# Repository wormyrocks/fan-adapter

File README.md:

# USB-PD fan driver

This is a completely untested, mostly routed PCB that uses a cheap MCU to trigger a 12V USB-PD sink, to drive a computer box fan. Entire BOM cost should only be $2-$3, no uncommon components. Might have to hand-solder the fan header. You could also use an angled fan header if you wanted.

I started designing this because I was annoyed about not having a desktop fume extractor that I could easily run off a laptop charger. I got busy / lazy and don't actually want to finish it, but if someone wants to adopt it that would be awesome! I have a handful of the CH32X035 preordered on JLCPCB, so the riskiest $10 of the project budget is already a sunk cost.

I designed this with 12V PWM fans in mind, but it occurs to me that if you want an amount of static pressure appropriate for fume extraction the move might be to use a 20V PDO. The SY8201 step-down should be able to support that no problem. Just make sure you don't plug it into a 12V fan then.

It is a Kicad 7 project. You could open and save it in Kicad 8 and force push it if you wanted, I don't care.

Designed to be as cheap as possible, using the [CH32X035 MCU](https://www.wch-ic.com/products/CH32X035.html).

99% of this design is derived from Stefan Wagner's repos:
https://github.com/wagiminator/Development-Boards
https://github.com/wagiminator/CH32X035-USB-PD-Adapter

Most firmware development could be done using the inbuilt USB bootloader or the [UCPD adapter](https://github.com/wagiminator/CH32X035-USB-PD-Adapter) sample code from Stefan Wagner. More simple example firmwares for CH32X035 live here: [CH32V003fun examples](https://github.com/cnlohr/ch32v003fun/tree/master/examples_x035)

There are LEDs to indicate the fan speed and two touch buttons to make it go faster and slower. Since there's a tach pin, you could do some pretty delightful UI stuff by making the line of LEDs strobe at the exact speed that the rotors are turning, which would make this into a fun desk toy.

I don't do a lot of work with motors and maybe would like someone to take a second look at the fan drive circuit. I followed [this](https://noctua.at/pub/media/wysiwyg/Noctua_PWM_specifications_white_paper.pdf) white paper. Do I need a flyback diode or something? More decoupling capacitors?

I remember spending a comically long time trying to find an in-stock LCSC alt for the 4-pin 2.54mm fan connector (Molex 470533000), it looks like it might be in "Molex actually defends that patent" territory. Oh well. Buy them on Amazon and solder them yourself, or knock yourself out on Aliexpress.
On the plus side, this means there are no through-hole parts, which will knock a day and a couple dollars off the final JLCPCB bill.

Evan Kahn 2025

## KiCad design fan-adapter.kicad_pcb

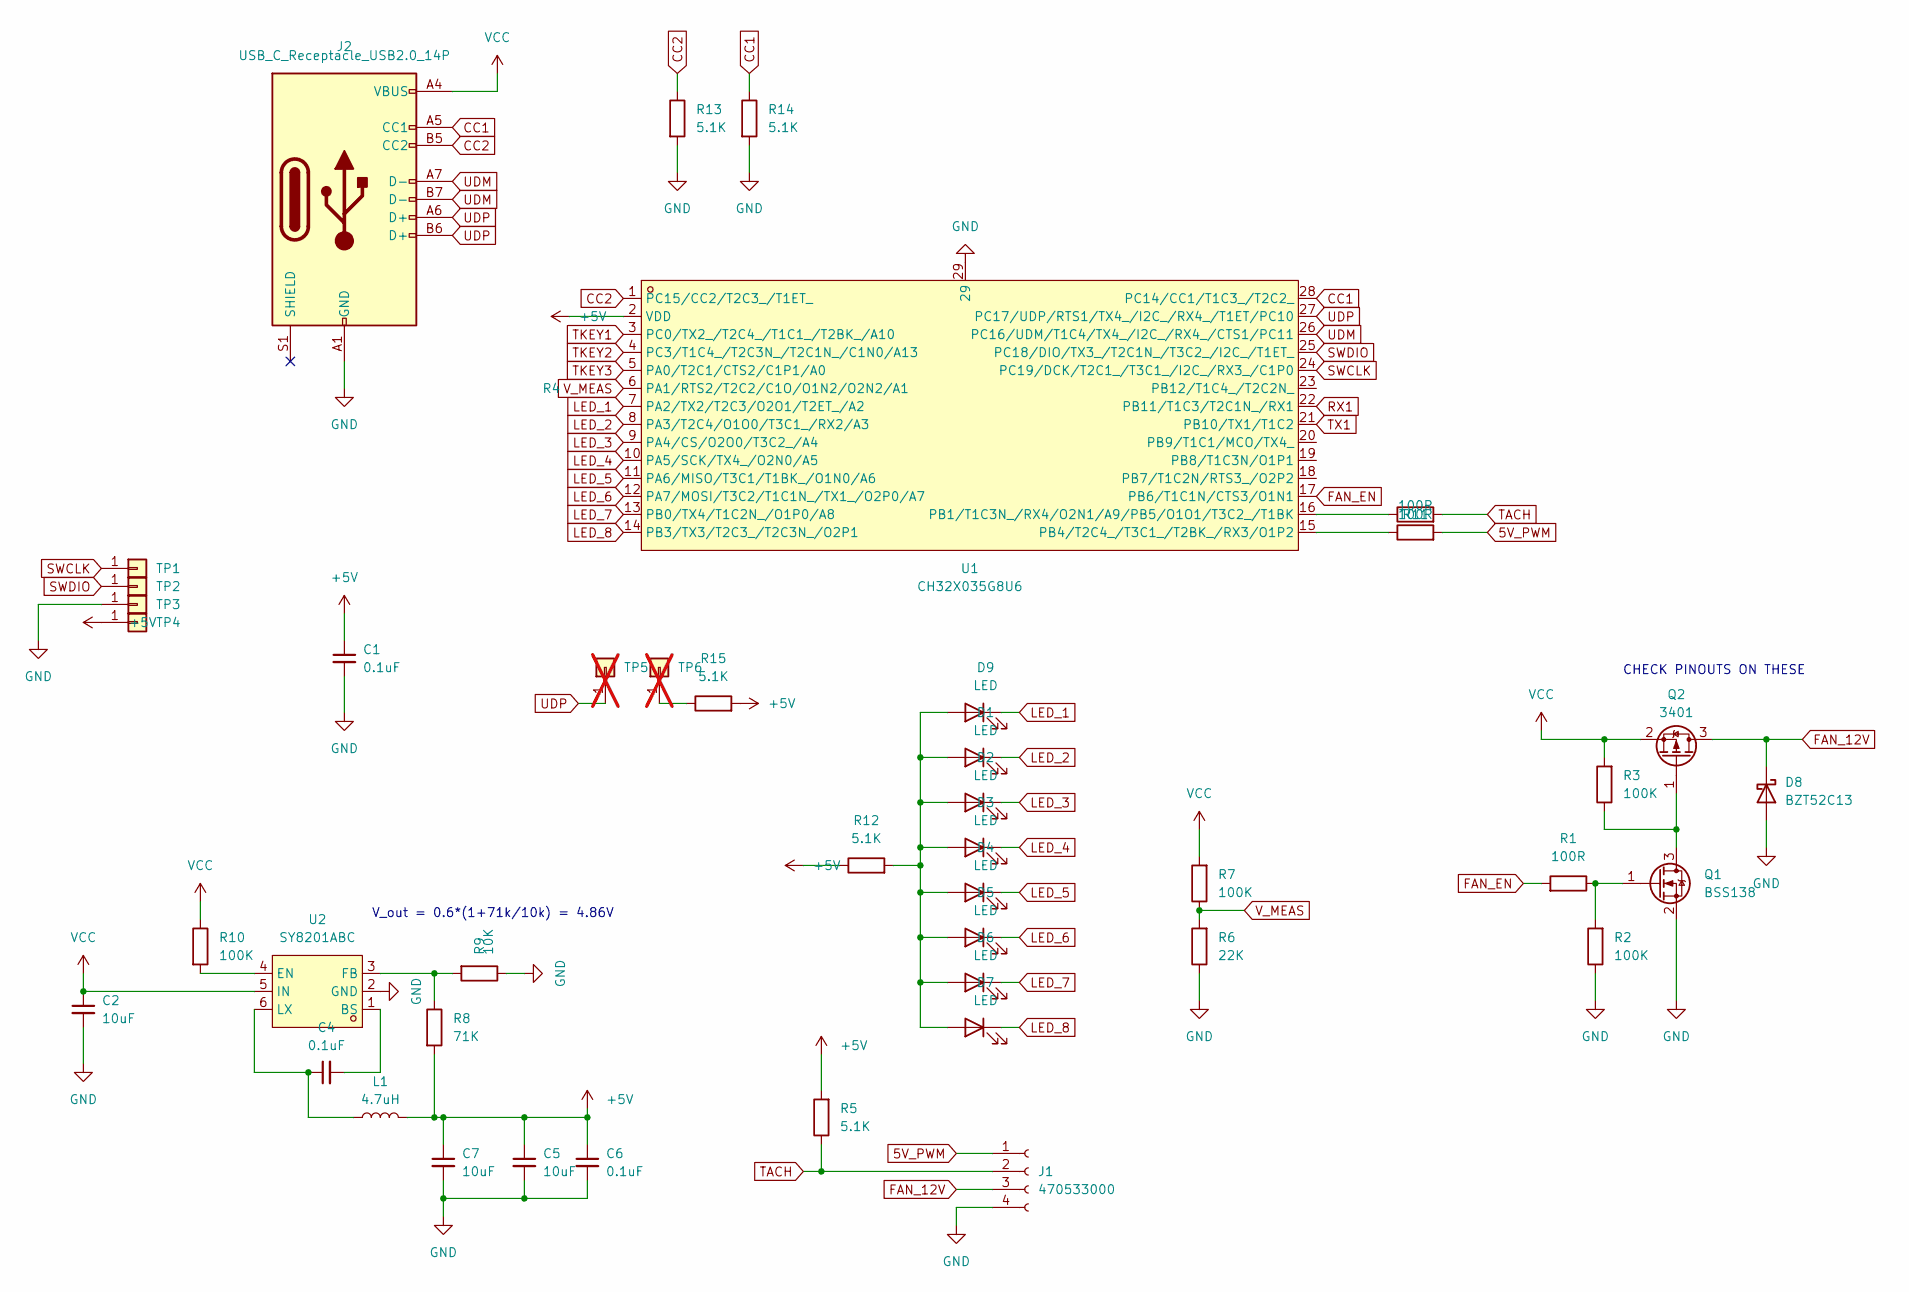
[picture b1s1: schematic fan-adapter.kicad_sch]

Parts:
C1, C4, C6: 0.1uF; C_0402_1005Metric
C2, C5, C7: 10uF; C_0805_2012Metric
D1, D2, D3, D4, D5, D6, D7, D9: LED; LED_0402_1005Metric
D8: BZT52C13; D_SOD-123; LCSC C173428
J1: 470533000; FanPinHeader_1x04_P2.54mm_Vertical; LCSC C19795120
J2: USB_C_Receptacle_USB2.0_14P; USB_C_Receptacle_HRO_TYPE-C-31-M-12; LCSC C223907
L1: 4.7uH; L_1210_3225Metric
Q1: BSS138; SOT-23
Q2: 3401; SOT-23; LCSC C7431448
R1, R4, R11: 100R; R_0402_1005Metric
R2, R3, R7, R10: 100K; R_0402_1005Metric
R5, R12, R13, R14, R15: 5.1K; R_0402_1005Metric
R6: 22K; R_0402_1005Metric
R8: 71K; R_0402_1005Metric
R9: 10K; R_0402_1005Metric
TP1, TP2, TP3, TP4: TEST_PAD; TestPoint_Pad_1.0x1.0mm
TP5, TP6: TEST_PAD; TestPoint_Pad_1.0x1.0mm; not fitted
U1: CH32X035G8U6; QFN-28_L4.0-W4.0-P0.40-BL-EP2.8; LCSC C7437027
U2: SY8201ABC; SOT-23-6; LCSC C108052

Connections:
5V_PWM: J1.1, R11.2
+5V: C1.1, C5.1, C6.1, C7.1, L1.2, R5.2, R8.2, R12.1, R15.2, TP4.1, U1.2 (VDD)
CC1: J2.A5 (CC1), R14.1, U1.28 (PC14/CC1/T1C3_/T2C2_)
CC2: J2.B5 (CC2), R13.1, U1.1 (PC15/CC2/T2C3_/T1ET_)
FAN_12V: D8.1 (K), J1.3, Q2.3 (D)
FAN_EN: R1.2, U1.17 (PB6/T1C1N/CTS3/O1N1)
GND: C1.2, C2.2, C5.2, C6.2, C7.2, D8.2 (A), J1.4, J2.A1 (GND), J2.A12 (GND), J2.B1 (GND), J2.B12 (GND), Q1.2 (S), R2.1, R6.1, R9.1, R13.2, R14.2, TP3.1, U1.29, U2.2 (GND)
LED_1: D9.1 (K), U1.7 (PA2/TX2/T2C3/O2O1/T2ET_/A2)
LED_2: D1.1 (K), U1.8 (PA3/T2C4/O1O0/T3C1_/RX2/A3)
LED_3: D2.1 (K), U1.9 (PA4/CS/O2O0/T3C2_/A4)
LED_4: D3.1 (K), U1.10 (PA5/SCK/TX4_/O2N0/A5)
LED_5: D4.1 (K), U1.11 (PA6/MISO/T3C1/T1BK_/O1N0/A6)
LED_6: D5.1 (K), U1.12 (PA7/MOSI/T3C2/T1C1N_/TX1_/O2P0/A7)
LED_7: D6.1 (K), U1.13 (PB0/TX4/T1C2N_/O1P0/A8)
LED_8: D7.1 (K), U1.14 (PB3/TX3/T2C3_/T2C3N_/O2P1)
unnamed: D1.2 (A), D2.2 (A), D3.2 (A), D4.2 (A), D5.2 (A), D6.2 (A), D7.2 (A), D9.2 (A), R12.2
unnamed: Q1.3 (D), Q2.1 (G), R3.1
unnamed: Q1.1 (G), R1.1, R2.2
unnamed: R15.1, TP6.1
unnamed: R4.1, U1.16 (PB1/T1C3N_/RX4/O2N1/A9/PB5/O1O1/T3C2_/T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)
unnamed: R11.1, U1.15 (PB4/T2C4_/T3C1_/T2BK_/RX3/O1P2)
unnamed: C4.2, U2.1 (BS)
unnamed: R10.2, U2.4 (EN)
unnamed: R8.1, R9.2, U2.3 (FB)
unnamed: C4.1, L1.1, U2.6 (LX)
RX1: U1.22 (PB11/T1C3/T2C1N_/RX1)
SWCLK: TP1.1, U1.24 (PC19/DCK/T2C1_/T3C1_/I2C_/RX3_/C1P0)
SWDIO: TP2.1, U1.25 (PC18/DIO/TX3_/T2C1N_/T3C2_/I2C_/T1ET_)
TACH: J1.2, R4.2, R5.1
TKEY1: U1.3 (PC0/TX2_/T2C4_/T1C1_/T2BK_/A10)
TKEY2: U1.4 (PC3/T1C4_/T2C3N_/T2C1N_/C1N0/A13)
TKEY3: U1.5 (PA0/T2C1/CTS2/C1P1/A0)
TX1: U1.21 (PB10/TX1/T1C2)
UDM: J2.A7 (D-), J2.B7 (D-), U1.26 (PC16/UDM/T1C4/TX4_/I2C_/RX4_/CTS1/PC11)
UDP: J2.A6 (D+), J2.B6 (D+), TP5.1, U1.27 (PC17/UDP/RTS1/TX4_/I2C_/RX4_/T1ET/PC10)
VCC: C2.1, J2.A4 (VBUS), J2.A9 (VBUS), J2.B4 (VBUS), J2.B9 (VBUS), Q2.2 (S), R3.2, R7.2, R10.1, U2.5 (IN)
V_MEAS: R6.2, R7.1, U1.6 (PA1/RTS2/T2C2/C1O/O1N2/O2N2/A1)

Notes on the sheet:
V_out = 0.6*(1+71k/10k) = 4.86V
CHECK PINOUTS ON THESE

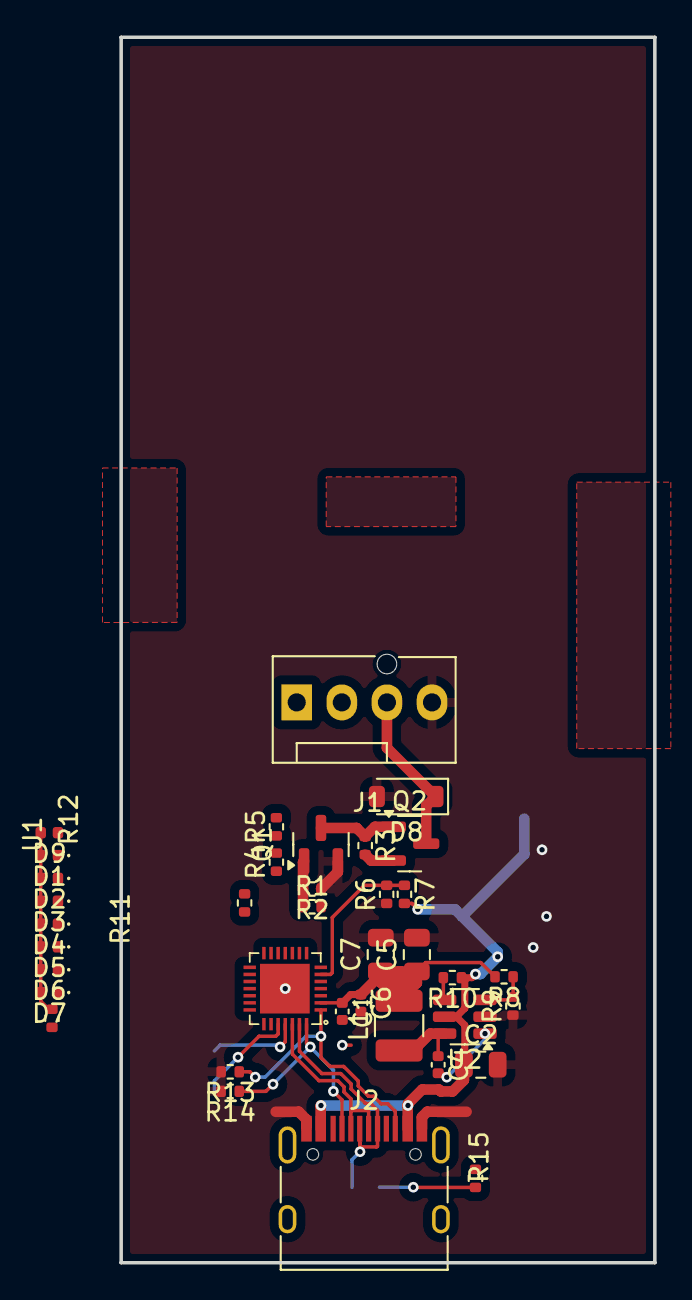
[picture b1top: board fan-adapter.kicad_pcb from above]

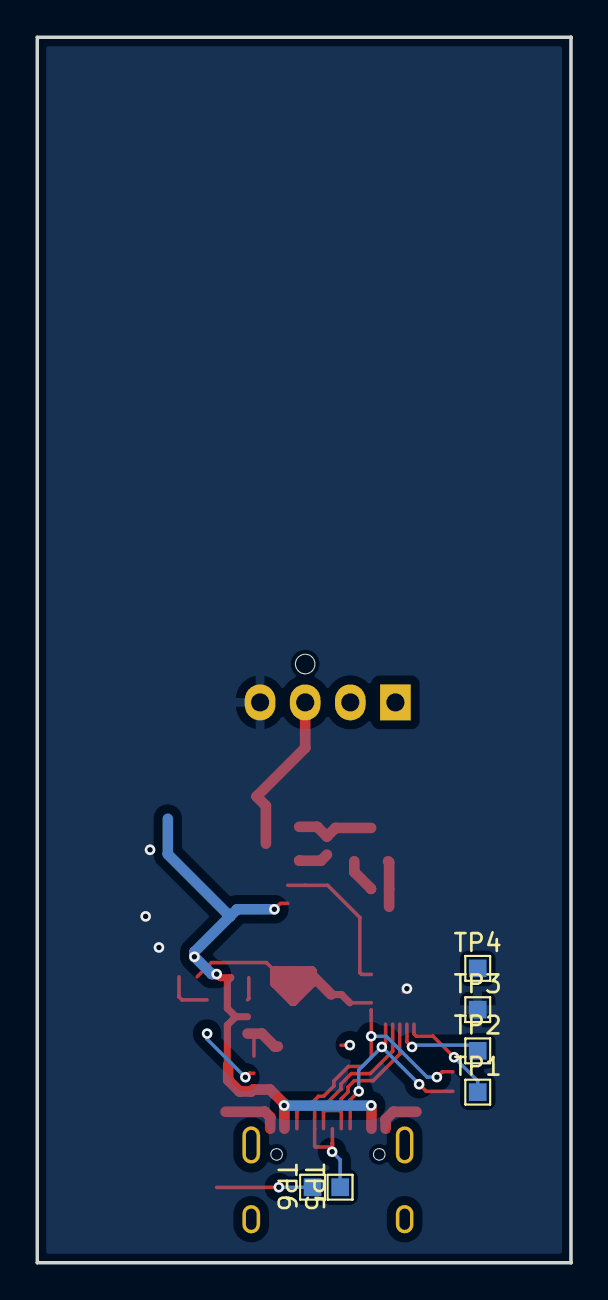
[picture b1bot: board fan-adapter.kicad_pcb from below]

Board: 2 copper layers, 30.0 x 69.0 mm, 43 parts (6 on the bottom side), 32 nets.
